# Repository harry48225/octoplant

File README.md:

# octoplant
Plant water indicator

octoplant helps you keep your plant hydrated. Using 12 LEDs it shows the current soil moisture level and allows you to set the water point so you can easily see how far off you are from the moisture level at which you normally water.

It's designed around an attiny824. A custom PCB combines it along with 12 LEDs, a wide trace that acts as a capacitive moisture sensor, a button, and a cr2032 battery (holder).

Simply press the button to light the leds. The soil moisture level is measured and then compared to the calibrated wet and dry points. By holding down the button you can save a moisture level and this led will blink on all further readings (I like to use this to save the level of moisture I usually water at). 

Built with:
 - Arduino (TinyMega core)
 - kicad
 - platform io
 
 [More info on hackaday](https://hackaday.io/project/187372/details/)

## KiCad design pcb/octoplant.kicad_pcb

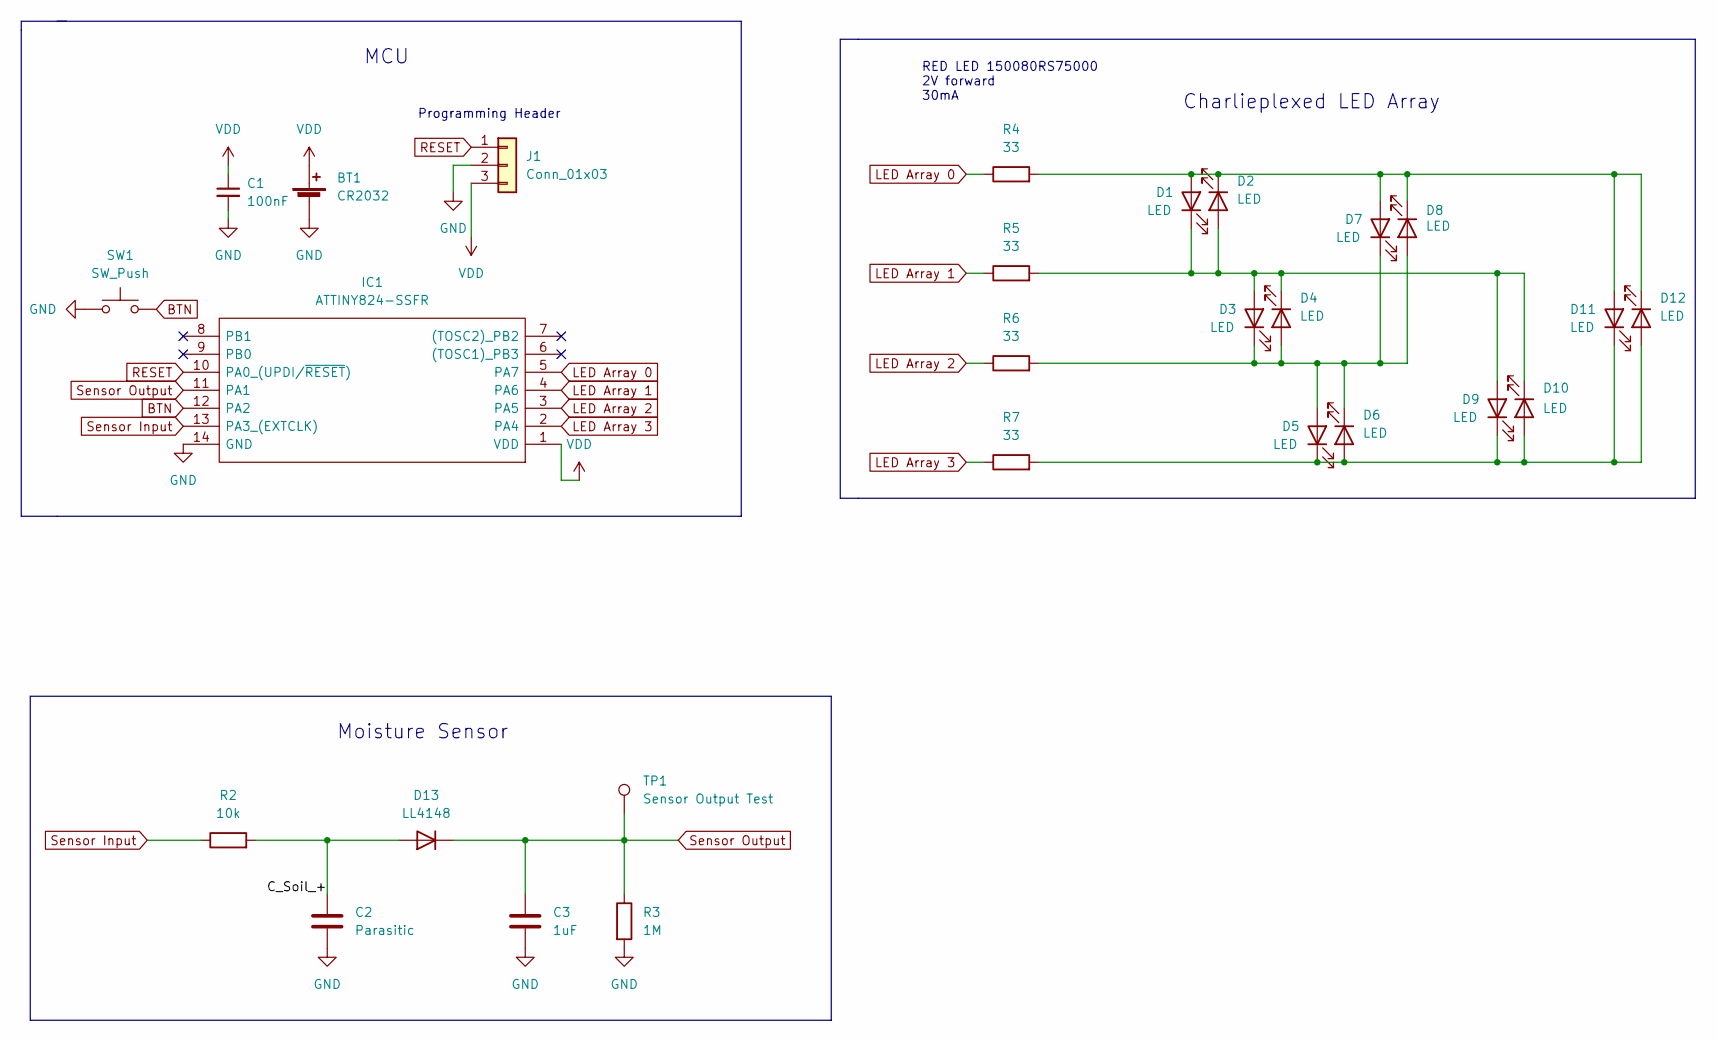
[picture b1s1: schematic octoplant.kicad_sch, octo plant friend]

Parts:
BT1: CR2032; BatteryHolder_Keystone_3002_1x2032
C1: 100nF; C_0805_2012Metric_Pad1.18x1.45mm_HandSolder
C2: Parasitic; soilCapactiorTrace
C3: 1uF; C_0805_2012Metric_Pad1.18x1.45mm_HandSolder
D1, D2, D3, D4, D5, D6, D7, D8, D9, D10, D11, D12: LED; LED_0805_2012Metric_Pad1.15x1.40mm_HandSolder
D13: LL4148; D_SC-80_HandSoldering
IC1: ATTINY824-SSFR; SOIC-14_3.9x8.7mm_P1.27mm; Manufacturer_Part_Number ATTINY824-SSFR; Mouser Part Number 579-ATTINY824-SSFR
J1: Conn_01x03; TestPoint_Pad_3x1_D1.5mm
R2: 10k; R_0805_2012Metric_Pad1.20x1.40mm_HandSolder
R3: 1M; R_0805_2012Metric_Pad1.20x1.40mm_HandSolder
R4, R5, R6, R7: 33; R_0805_2012Metric_Pad1.20x1.40mm_HandSolder
SW1: SW_Push; SW_Push_1P1T_NO_CK_KSC6xxJ
TP1: Sensor Output Test; TestPoint_Pad_D1.5mm

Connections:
/C_Soil_+: C2.1, D13.2 (A), R2.2
BTN: IC1.12 (PA2), SW1.2
GND: BT1.2 (-), C1.2, C2.2, C3.2, IC1.14 (GND), J1.2, R3.2, SW1.1
LED Array 0: IC1.5 (PA7), R4.1
LED Array 1: IC1.4 (PA6), R5.1
LED Array 2: IC1.3 (PA5), R6.1
LED Array 3: IC1.2 (PA4), R7.1
unnamed: D1.1 (K), D2.2 (A), D3.2 (A), D4.1 (K), D9.2 (A), D10.1 (K), R5.2
unnamed: D1.2 (A), D2.1 (K), D7.2 (A), D8.1 (K), D11.2 (A), D12.1 (K), R4.2
unnamed: D3.1 (K), D4.2 (A), D5.2 (A), D6.1 (K), D7.1 (K), D8.2 (A), R6.2
unnamed: D5.1 (K), D6.2 (A), D9.1 (K), D10.2 (A), D11.1 (K), D12.2 (A), R7.2
RESET: IC1.10 (PA0_(UPDI/~RESET)), J1.1
Sensor Input: IC1.13 (PA3_(EXTCLK)), R2.1
Sensor Output: C3.1, D13.1 (K), IC1.11 (PA1), R3.1, TP1.1
VDD: BT1.1 (+), C1.1, IC1.1 (VDD), J1.3

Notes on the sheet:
RED LED 150080RS75000 2V forward 30mA
Charlieplexed LED Array
Programming Header
Moisture Sensor
MCU

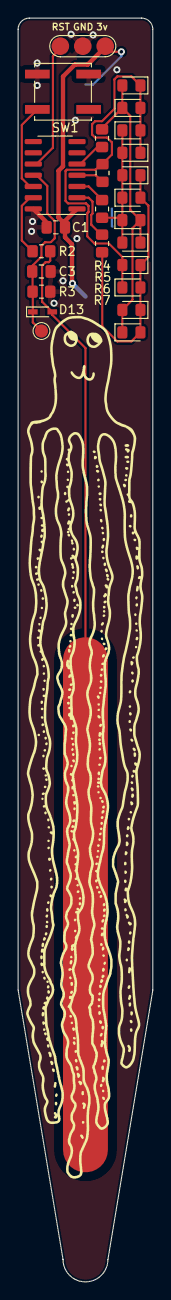
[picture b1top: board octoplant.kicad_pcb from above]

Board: 2 copper layers, 15.2 x 143.0 mm, 27 parts (1 on the bottom side), 15 nets.

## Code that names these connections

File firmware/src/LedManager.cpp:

#include "LedManager.h"
#include <Arduino.h>

namespace LedManager {
  /*  Manages the charlieplexed leds */
  int _pins[4] = {PIN_PA7, PIN_PA6, PIN_PA5, PIN_PA4};
  int _ledEnable[12] = {0,0,0,0,0,0,0,0,0,0,0,0};
  // 255 is on, < 127 is off
  int _ledState[12] = {0,0,0,0,0,0,0,0,0,0,0,0};
  // Gets subtracted from the led state each cycle
  int _flashModifier[12] = {0,0,0,0,0,0,0,0,0,0,0,0};
  int _currentLed = 0;

  void _openCurrentPath(int from, int to) {
    pinMode(_pins[from], OUTPUT);
    pinMode(_pins[to], OUTPUT);
    digitalWrite(_pins[from], HIGH);
    digitalWrite(_pins[to], LOW);
  }

  void _closeCurrentPaths() {
    pinMode(_pins[0], INPUT);  
    pinMode(_pins[1], INPUT);  
    pinMode(_pins[2], INPUT);  
    pinMode(_pins[3], INPUT);
  }

  void turnOnLed(int ledNumber) {
    if (_ledEnable[ledNumber] == 0) {
      _ledEnable[ledNumber] = 1;
      _ledState[ledNumber] = 255;
    }
  }

  void turnOffLed(int ledNumber) {
    // turns off an led
    if (_ledEnable[ledNumber] == 1) {
      _ledEnable[ledNumber] = 0;
      _ledState[ledNumber] = 0;
    }
  }

  void flashLed(int ledNumber, FlashRate rate) {
    int rateNumber = 0;
    switch (rate) {
      case (FlashRate::NONE):
        rateNumber = 0;
        break;
      case (FlashRate::SLOW):
        rateNumber = 4;
        break;
      case (FlashRate::MEDIUM):
        rateNumber = 16;
        break;
      case (FlashRate::FAST):
        rateNumber = 32;
        break;
    }
    _flashModifier[ledNumber] = rateNumber;
    _ledEnable[ledNumber] = 1;
  }

  void resetLeds() {
    for (int i = 0; i < 12; i++) {
      flashLed(i, FlashRate::NONE);
      turnOffLed(i);
    }
  }

  void _createCurrentPathForLed(int ledNumber) {
    switch (ledNumber) {
      case 0:
        _openCurrentPath(0,1);
        break; 
      case 6:
        _openCurrentPath(0,2);
        break;
      case 10:
        _openCurrentPath(0,3);
        break; 
      case 1:
        _openCurrentPath(1,0);
        break;
      case 2:
        _openCurrentPath(1,2);
        break; 
      case 8:
        _openCurrentPath(1,3);
        break;
      case 7:
        _openCurrentPath(2,0);
        break; 
      case 3:
        _openCurrentPath(2,1);
        break;
      case 4:
        _openCurrentPath(2,3);
        break; 
      case 11:
        _openCurrentPath(3,0);
        break;
      case 9:
        _openCurrentPath(3,1);
        break; 
      case 5:
        _openCurrentPath(3,2);
        break;    
    }
  }

  void setup() {
    // There is a 64 prescaler on TCA0
    TCA0.SPLIT.LPER = 0xFF; // Count down from 0xFF (255), At 10MHz  (10MHz/255)/64 ~ 600Hz
    TCA0.SPLIT.LCMP0 = 0xFF; // Trigger interrupt after full count
    TCA0.SPLIT.INTCTRL |= 0x10; // Enable interrupt on LCMP0
  }

  // Triggers ~600Hz -- This is probably too high given how much computation happens in the ISR
  ISR(TCA0_LCMP0_vect) {
    TCA0.SPLIT.INTFLAGS = 0xFF; // Clear the int flags otherwise millis breaks
    _closeCurrentPaths();

    if (_ledEnable[_currentLed] == 1) {
      if (_ledState[_currentLed] < _flashModifier[_currentLed]) {
        _ledState[_currentLed] = 255 - (_flashModifier[_currentLed] - _ledState[_currentLed]);
      } else {
        _ledState[_currentLed] -= _flashModifier[_currentLed];
      }

      if (_ledState[_currentLed] > 127)
      {
        _createCurrentPathForLed(_currentLed);
      }
    }

    _currentLed = (_currentLed + 1) % 12; 
  }
}

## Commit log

2022-03-14 Add silkscreen art
2022-03-14 Change button pin to a fully async one
2022-03-15 resize capacitor pad
2022-03-15 Finalise pcb
2022-04-03 Tweak pcb
2022-04-03 Add platform io and basic firmware
2022-04-03 Add led helper methods
2022-04-03 Refactor moisture readings
2022-04-03 Basic button test
2022-04-03 Add rough sleep
2022-04-03 Cleanup sleep manager
2022-04-04 Remove ability to wake before sleeping
2022-04-04 Increase led frequency
2022-04-04 Add led flashing
2022-04-04 Refactor led flashing
2022-04-04 Add eeprom config storage
2022-04-04 Add calibration
2022-04-04 Add ability to enter calibration mode
2022-04-04 Refactor calibration code
2022-04-04 Only enter calibration mode on powerup
2022-04-04 fix sleep mode
2022-04-05 Add delay to stabilise moisture readnig
2022-04-05 Increase awake time
2022-04-05 Add water point setting
2022-04-05 Refactor code
2022-04-05 Fix sleep?
2022-10-05 Add hackaday link
2022-10-05 fix hackaday link
2022-10-05 add schematic
